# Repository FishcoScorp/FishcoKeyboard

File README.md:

# FishcoKeyboard
My keyboard for the program fallout by hackclub\
\
This keyboard was made with convieniece in mind, with 15 customizable macro keys (4 on left 11 on right) as well as a volume dial and small screen. 

# Table of Contents
Bill of Materials: https://github.com/FishcoScorp/FishcoKeyboard/edit/main/README.md#:~:text=Build_Files-,BOM,-.csv \
Photo Gallery: https://github.com/FishcoScorp/FishcoKeyboard/edit/main/README.md#:~:text=Fallout%20Zine.md-,Photo,-Gallery.md \
Code: https://github.com/FishcoScorp/FishcoKeyboard/edit/main/README.md#:~:text=README.md-,code,-.py \
Zine: https://github.com/FishcoScorp/FishcoKeyboard/edit/main/README.md#:~:text=BOM.csv-,Fallout,-Zine.md \
\
I am also in the process of working on a software that will interface with the keyboard and allow me to easily switch macro keys and the display on the screen, and make it easy to flash new code to the keyboard.\
\

\
How to put it together! \
I used Kicad, and started by making a matrix with all the keys at about where I thought they were on a subsheet. That looks like this (Don't forget to add diodes too!!!) This works by wiring rows and columns which, when shorted by pressing a button, can be identified and pinpointed similar to using x and y on a graph so that it sends the correct input to your device!

\
Then I have the main schematic sheet, where I make all the rest of the connections. Using tags I connect the matrix to the ESP and also the screen and rotary encoder. Notice I connect the grounds of the latter two elements using a GND tag. This is because I am going to use a gnd fill later, which means the board will be coated in a thin layer of copper, removing the need for GND connections as this coating will serve that purpose.

\
Now bring it over to the PCB editor, where you will shape what your keyboard looks like. You can use an app called KB Placer by creating a layout beforehand on the website http://keyboard-layout-editor.com/ and then importing the JSON to KB placer. However, this did not work for me so I had to manually place everything and create the outline of the keyboard myself. I then connected the matrix, rotary encoder, and screen before adding the GND fill (the red in this photo)

\
Then it was time to cad a case. I used Fusion, using the exported .step file model to draw an outline for my case. Then I added some standoffs using the PCB as a reference with the screw holes I had placed earlier, ensuring stabilization but not breaking the PCB. In this case I made so both the bottom and top had walls so that it would look clean and sleek. I also sunk the keys into the keyboard a little so that it would look slim and cool. I also added a window into the ESP cause I think it would look really cool to be abe to see it, a little glimpse into the work/electronics that are required to make this a reality.

\ 
After this I designed my zine and submitted it, and here we are!

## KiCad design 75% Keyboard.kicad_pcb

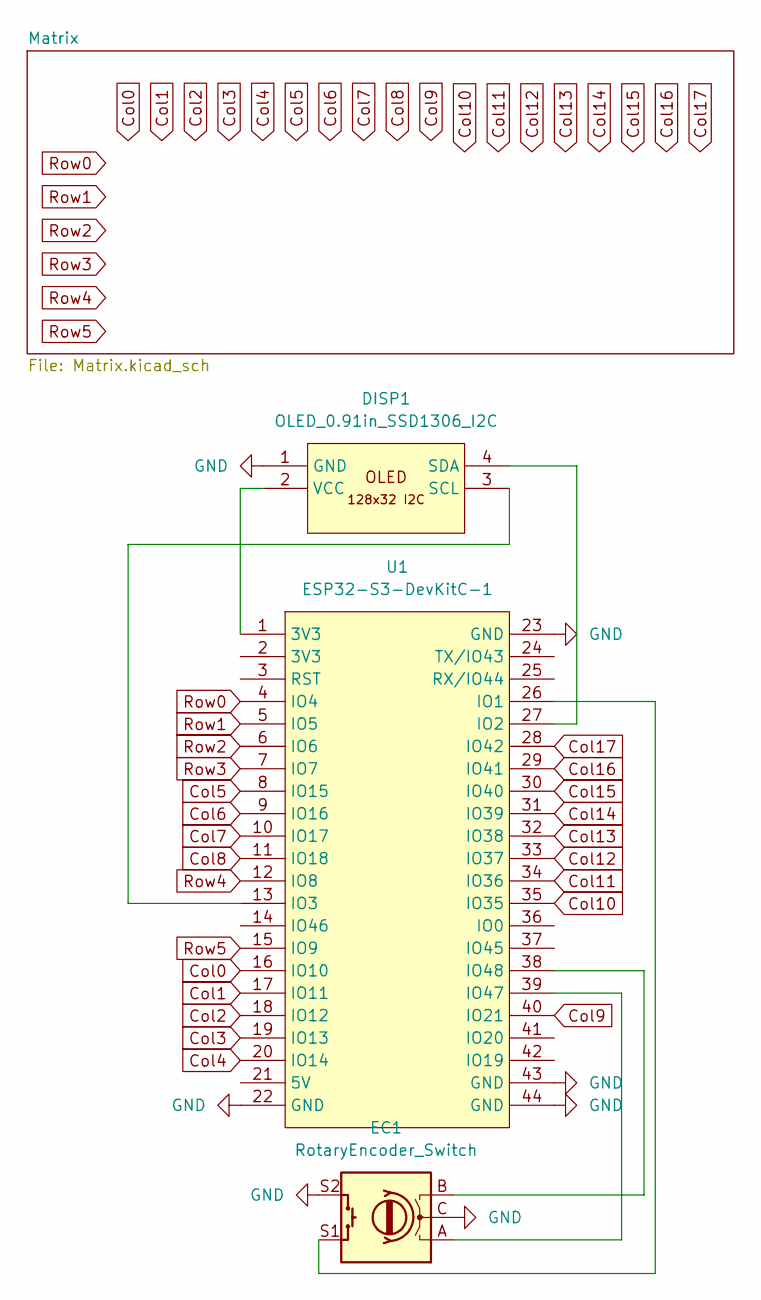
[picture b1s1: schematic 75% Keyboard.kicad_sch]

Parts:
DISP1: OLED_0.91in_SSD1306_I2C; OLED_0.91in_SSD1306_I2C_4Pin_P2.54mm
EC1: RotaryEncoder_Switch; RotaryEncoder_Alps_EC11E-Switch_Vertical_H20mm_MountingHoles
U1: ESP32-S3-DevKitC-1; ESP32-S3-DevKitC-1_2x22_P2.54mm

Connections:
Col0: U1.16 (IO10); also elsewhere on the board
Col1: U1.17 (IO11); also elsewhere on the board
Col2: U1.18 (IO12); also elsewhere on the board
Col3: U1.19 (IO13); also elsewhere on the board
Col4: U1.20 (IO14); also elsewhere on the board
Col5: U1.8 (IO15); also elsewhere on the board
Col6: U1.9 (IO16); also elsewhere on the board
Col7: U1.10 (IO17); also elsewhere on the board
Col8: U1.11 (IO18); also elsewhere on the board
Col9: U1.40 (IO21); also elsewhere on the board
Col10: U1.35 (IO35); also elsewhere on the board
Col11: U1.34 (IO36); also elsewhere on the board
Col12: U1.33 (IO37); also elsewhere on the board
Col13: U1.32 (IO38); also elsewhere on the board
Col14: U1.31 (IO39); also elsewhere on the board
Col15: U1.30 (IO40); also elsewhere on the board
Col16: U1.29 (IO41); also elsewhere on the board
Col17: U1.28 (IO42); also elsewhere on the board
GND: DISP1.1 (GND), EC1.C, EC1.S2, U1.22 (GND), U1.23 (GND), U1.43 (GND), U1.44 (GND)
unnamed: DISP1.3 (SCL), U1.13 (IO3)
unnamed: DISP1.4 (SDA), U1.27 (IO2)
unnamed: DISP1.2 (VCC), U1.1 (3V3)
unnamed: EC1.S1, U1.26 (IO1)
unnamed: EC1.A, U1.39 (IO47)
unnamed: EC1.B, U1.38 (IO48)
Row0: U1.4 (IO4); also elsewhere on the board
Row1: U1.5 (IO5); also elsewhere on the board
Row2: U1.6 (IO6); also elsewhere on the board
Row3: U1.7 (IO7); also elsewhere on the board
Row4: U1.12 (IO8); also elsewhere on the board
Row5: U1.15 (IO9); also elsewhere on the board

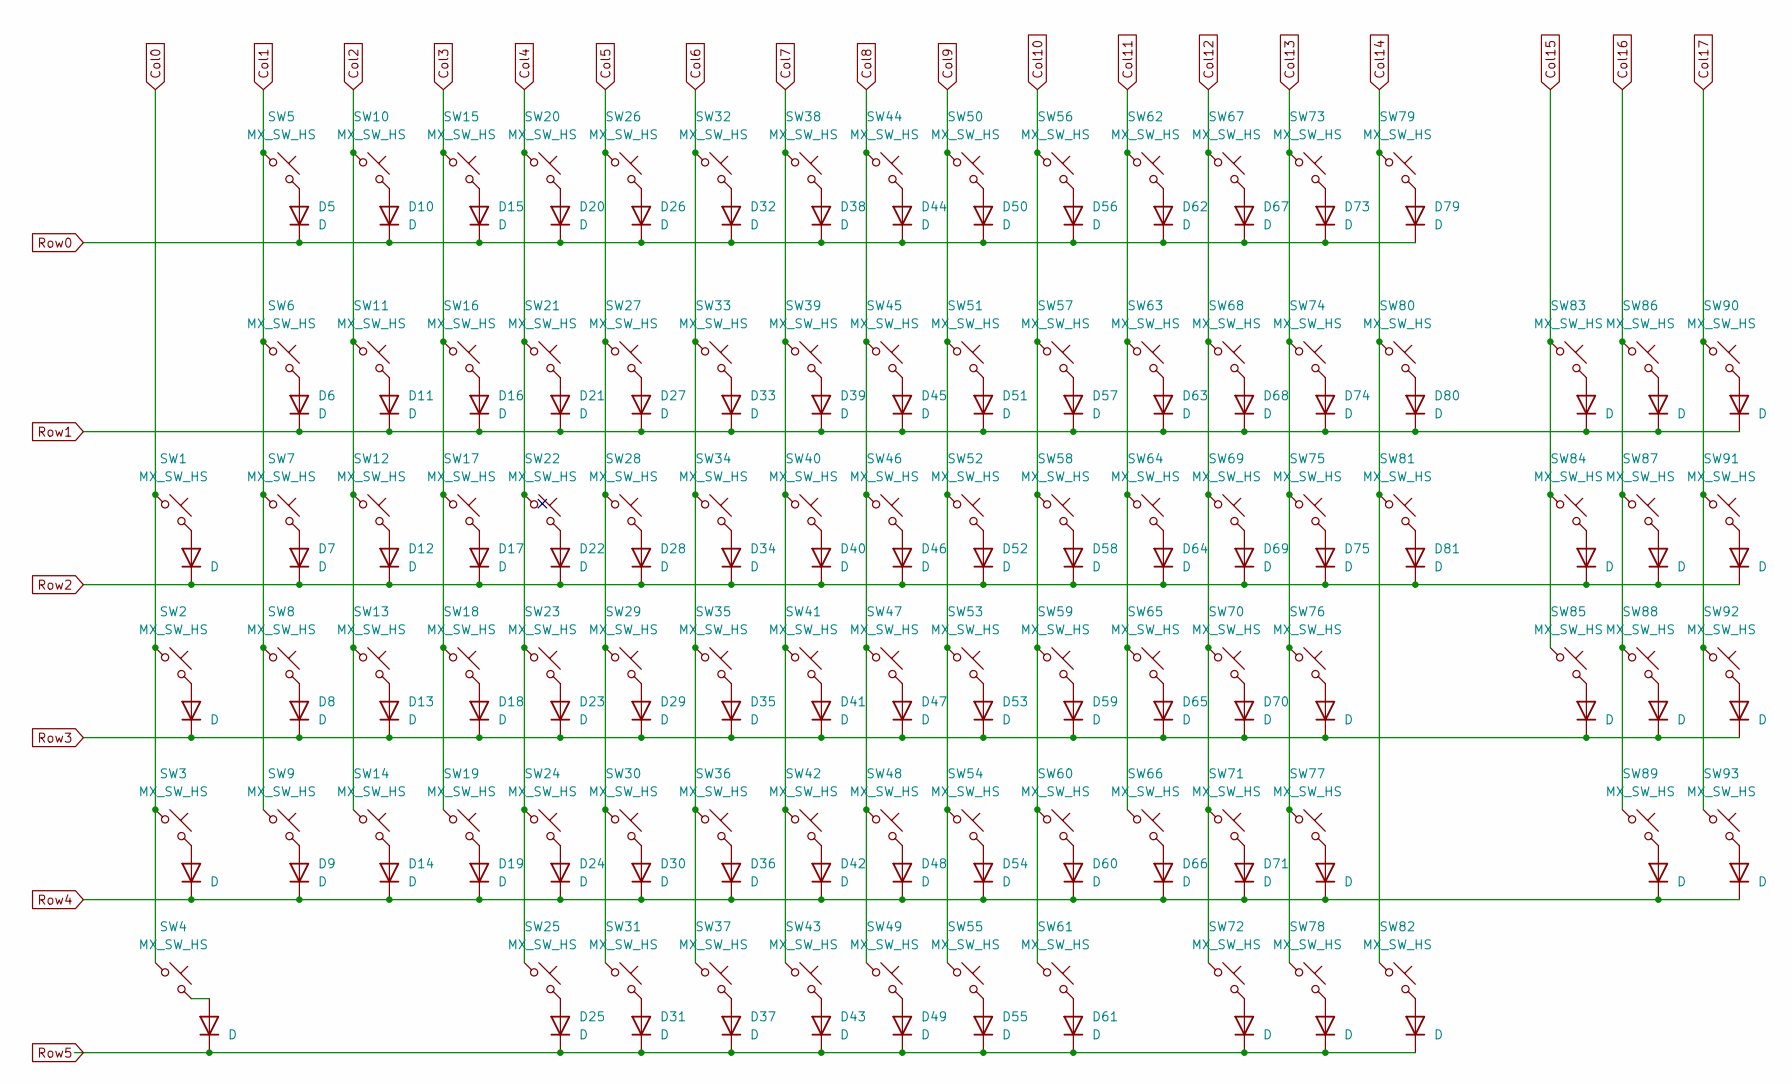
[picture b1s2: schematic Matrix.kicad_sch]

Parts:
D1, D2, D3, D4, D5, D6, D7, D8, D9, D10, D11, D12, D13, D14, D15, D16, D17, D18, D19, D20, D21, D22, D23, D24, D25, D26, D27, D28, D29, D30, D31, D32, D33, D34, D35, D36, D37, D38, D39, D40, D41, D42, D43, D44, D45, D46, D47, D48, D49, D50, D51, D52, D53, D54, D55, D56, D57, D58, D59, D60, D61, D62, D63, D64, D65, D66, D67, D68, D69, D70, D71, D72, D73, D74, D75, D76, D77, D78, D79, D80, D81, D82, D83, D84, D85, D86, D87, D88, D89, D90, D91, D92, D93: D; D_SOD-123
SW1, SW2, SW3, SW4, SW5, SW6, SW10, SW11, SW12, SW13, SW14, SW15, SW16, SW17, SW18, SW19, SW20, SW21, SW22, SW23, SW24, SW26, SW27, SW28, SW29, SW30, SW32, SW33, SW34, SW35, SW36, SW38, SW39, SW40, SW41, SW42, SW44, SW45, SW46, SW47, SW48, SW49, SW50, SW51, SW52, SW53, SW54, SW55, SW56, SW57, SW58, SW59, SW60, SW61, SW62, SW63, SW64, SW65, SW66, SW67, SW68, SW69, SW70, SW72, SW73, SW74, SW75, SW77, SW78, SW79, SW82, SW83, SW84, SW85, SW86, SW87, SW88, SW89, SW90, SW91, SW92, SW93: MX_SW_HS; SW_Cherry_MX_1.00u_PCB
SW7, SW81: MX_SW_HS; SW_Cherry_MX_1.50u_PCB
SW8, SW71: MX_SW_HS; SW_Cherry_MX_1.75u_PCB
SW9, SW76: MX_SW_HS; SW_Cherry_MX_2.25u_PCB
SW25, SW31, SW37: MX_SW_HS; SW_Cherry_MX_1.25u_PCB
SW43: MX_SW_HS; SW_Cherry_MX_6.25u_PCB
SW80: MX_SW_HS; SW_Cherry_MX_2.00u_PCB

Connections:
Col0: SW1.1, SW2.1, SW3.1, SW4.1; also elsewhere on the board
Col1: SW5.1, SW6.1, SW7.1, SW8.1, SW9.1; also elsewhere on the board
Col2: SW10.1, SW11.1, SW12.1, SW13.1, SW14.1; also elsewhere on the board
Col3: SW15.1, SW16.1, SW17.1, SW18.1, SW19.1; also elsewhere on the board
Col4: SW20.1, SW21.1, SW22.1, SW23.1, SW24.1, SW25.1; also elsewhere on the board
Col5: SW26.1, SW27.1, SW28.1, SW29.1, SW30.1, SW31.1; also elsewhere on the board
Col6: SW32.1, SW33.1, SW34.1, SW35.1, SW36.1, SW37.1; also elsewhere on the board
Col7: SW38.1, SW39.1, SW40.1, SW41.1, SW42.1, SW43.1; also elsewhere on the board
Col8: SW44.1, SW45.1, SW46.1, SW47.1, SW48.1, SW49.1; also elsewhere on the board
Col9: SW50.1, SW51.1, SW52.1, SW53.1, SW54.1, SW55.1; also elsewhere on the board
Col10: SW56.1, SW57.1, SW58.1, SW59.1, SW60.1, SW61.1; also elsewhere on the board
Col11: SW62.1, SW63.1, SW64.1, SW65.1, SW66.1; also elsewhere on the board
Col12: SW67.1, SW68.1, SW69.1, SW70.1, SW71.1, SW72.1; also elsewhere on the board
Col13: SW73.1, SW74.1, SW75.1, SW76.1, SW77.1, SW78.1; also elsewhere on the board
Col14: SW79.1, SW80.1, SW81.1, SW82.1; also elsewhere on the board
Col15: SW83.1, SW84.1, SW85.1; also elsewhere on the board
Col16: SW86.1, SW87.1, SW88.1, SW89.1; also elsewhere on the board
Col17: SW90.1, SW91.1, SW92.1, SW93.1; also elsewhere on the board
unnamed: D1.2 (A), SW1.2
unnamed: D2.2 (A), SW2.2
unnamed: D3.2 (A), SW3.2
unnamed: D4.2 (A), SW4.2
unnamed: D5.2 (A), SW5.2
unnamed: D6.2 (A), SW6.2
unnamed: D7.2 (A), SW7.2
unnamed: D8.2 (A), SW8.2
unnamed: D9.2 (A), SW9.2
unnamed: D10.2 (A), SW10.2
unnamed: D11.2 (A), SW11.2
unnamed: D12.2 (A), SW12.2
unnamed: D13.2 (A), SW13.2
unnamed: D14.2 (A), SW14.2
unnamed: D15.2 (A), SW15.2
unnamed: D16.2 (A), SW16.2
unnamed: D17.2 (A), SW17.2
unnamed: D18.2 (A), SW18.2
unnamed: D19.2 (A), SW19.2
unnamed: D20.2 (A), SW20.2
unnamed: D21.2 (A), SW21.2
unnamed: D22.2 (A), SW22.2
unnamed: D23.2 (A), SW23.2
unnamed: D24.2 (A), SW24.2
unnamed: D25.2 (A), SW25.2
unnamed: D26.2 (A), SW26.2
unnamed: D27.2 (A), SW27.2
unnamed: D28.2 (A), SW28.2
unnamed: D29.2 (A), SW29.2
unnamed: D30.2 (A), SW30.2
unnamed: D31.2 (A), SW31.2
unnamed: D32.2 (A), SW32.2
unnamed: D33.2 (A), SW33.2
unnamed: D34.2 (A), SW34.2
unnamed: D35.2 (A), SW35.2
unnamed: D36.2 (A), SW36.2
unnamed: D37.2 (A), SW37.2
unnamed: D38.2 (A), SW38.2
unnamed: D39.2 (A), SW39.2
unnamed: D40.2 (A), SW40.2
unnamed: D41.2 (A), SW41.2
unnamed: D42.2 (A), SW42.2
unnamed: D43.2 (A), SW43.2
unnamed: D44.2 (A), SW44.2
unnamed: D45.2 (A), SW45.2
unnamed: D46.2 (A), SW46.2
unnamed: D47.2 (A), SW47.2
unnamed: D48.2 (A), SW48.2
unnamed: D49.2 (A), SW49.2
unnamed: D50.2 (A), SW50.2
unnamed: D51.2 (A), SW51.2
unnamed: D52.2 (A), SW52.2
unnamed: D53.2 (A), SW53.2
unnamed: D54.2 (A), SW54.2
unnamed: D55.2 (A), SW55.2
unnamed: D56.2 (A), SW56.2
unnamed: D57.2 (A), SW57.2
unnamed: D58.2 (A), SW58.2
unnamed: D59.2 (A), SW59.2
unnamed: D60.2 (A), SW60.2
unnamed: D61.2 (A), SW61.2
unnamed: D62.2 (A), SW62.2
unnamed: D63.2 (A), SW63.2
unnamed: D64.2 (A), SW64.2
unnamed: D65.2 (A), SW65.2
unnamed: D66.2 (A), SW66.2
unnamed: D67.2 (A), SW67.2
unnamed: D68.2 (A), SW68.2
unnamed: D69.2 (A), SW69.2
unnamed: D70.2 (A), SW70.2
unnamed: D71.2 (A), SW71.2
unnamed: D72.2 (A), SW72.2
unnamed: D73.2 (A), SW73.2
unnamed: D74.2 (A), SW74.2
unnamed: D75.2 (A), SW75.2
unnamed: D76.2 (A), SW76.2
unnamed: D77.2 (A), SW77.2
unnamed: D78.2 (A), SW78.2
unnamed: D79.2 (A), SW79.2
unnamed: D80.2 (A), SW80.2
unnamed: D81.2 (A), SW81.2
unnamed: D82.2 (A), SW82.2
unnamed: D83.2 (A), SW83.2
unnamed: D84.2 (A), SW84.2
unnamed: D85.2 (A), SW85.2
unnamed: D86.2 (A), SW86.2
unnamed: D87.2 (A), SW87.2
unnamed: D88.2 (A), SW88.2
unnamed: D89.2 (A), SW89.2
unnamed: D90.2 (A), SW90.2
unnamed: D91.2 (A), SW91.2
unnamed: D92.2 (A), SW92.2
unnamed: D93.2 (A), SW93.2
Row0: D5.1 (K), D10.1 (K), D15.1 (K), D20.1 (K), D26.1 (K), D32.1 (K), D38.1 (K), D44.1 (K), D50.1 (K), D56.1 (K), D62.1 (K), D67.1 (K), D73.1 (K), D79.1 (K); also elsewhere on the board
Row1: D6.1 (K), D11.1 (K), D16.1 (K), D21.1 (K), D27.1 (K), D33.1 (K), D39.1 (K), D45.1 (K), D51.1 (K), D57.1 (K), D63.1 (K), D68.1 (K), D74.1 (K), D80.1 (K), D83.1 (K), D86.1 (K), D90.1 (K); also elsewhere on the board
Row2: D1.1 (K), D7.1 (K), D12.1 (K), D17.1 (K), D22.1 (K), D28.1 (K), D34.1 (K), D40.1 (K), D46.1 (K), D52.1 (K), D58.1 (K), D64.1 (K), D69.1 (K), D75.1 (K), D81.1 (K), D84.1 (K), D87.1 (K), D91.1 (K); also elsewhere on the board
Row3: D2.1 (K), D8.1 (K), D13.1 (K), D18.1 (K), D23.1 (K), D29.1 (K), D35.1 (K), D41.1 (K), D47.1 (K), D53.1 (K), D59.1 (K), D65.1 (K), D70.1 (K), D76.1 (K), D85.1 (K), D88.1 (K), D92.1 (K); also elsewhere on the board
Row4: D3.1 (K), D9.1 (K), D14.1 (K), D19.1 (K), D24.1 (K), D30.1 (K), D36.1 (K), D42.1 (K), D48.1 (K), D54.1 (K), D60.1 (K), D66.1 (K), D71.1 (K), D77.1 (K), D89.1 (K), D93.1 (K); also elsewhere on the board
Row5: D4.1 (K), D25.1 (K), D31.1 (K), D37.1 (K), D43.1 (K), D49.1 (K), D55.1 (K), D61.1 (K), D72.1 (K), D78.1 (K), D82.1 (K); also elsewhere on the board

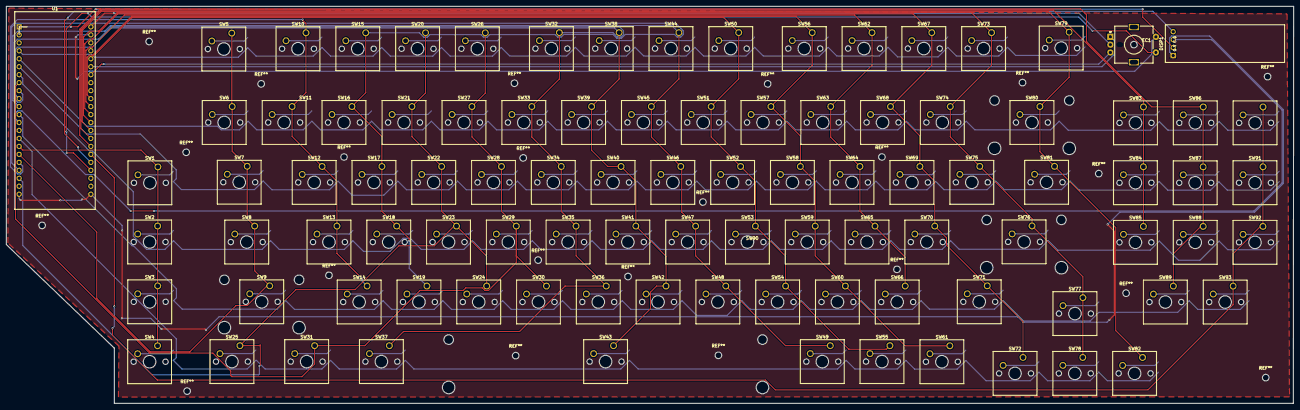
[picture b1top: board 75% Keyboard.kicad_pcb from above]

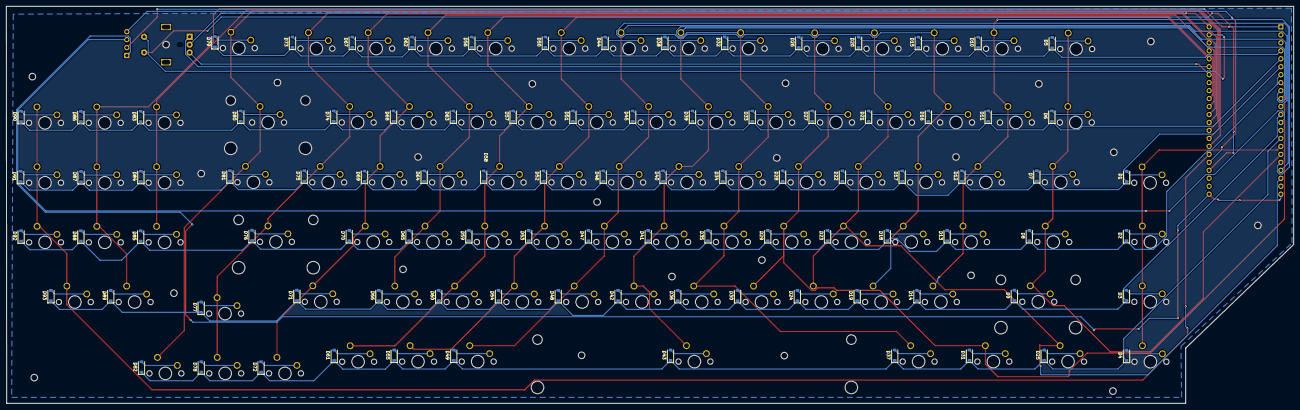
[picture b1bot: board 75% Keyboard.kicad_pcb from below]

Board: 2 copper layers, 410.2 x 126.5 mm, 189 parts (93 on the bottom side), 124 nets.

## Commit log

2026-04-20 Format BOM.md for better readability
2026-04-20 Fix formatting and update purchase links in BOM.md
2026-04-20 Add keyboard matrix and rotary encoder functionality
    Implement a keyboard matrix with rotary encoder support and OLED display.
2026-04-20 Update BOM with new materials and costs
2026-04-20 Add PETG material link to BOM
2026-04-27 Rename 75% Keyboard.kicad_pcb to Build_Files/75% Keyboard.kicad_pcb
2026-04-27 Rename 75% Keyboard.kicad_pcb.zip to Build_Files /75%Keyboard.kicad_pcb.zip
2026-04-27 Rename Fallout Zine (1).png to Fallout Zine.png
2026-04-27 Rename Fallout Zine.png to Fallout Zine.md
2026-04-27 Insert image in Fallout Zine.md
    Add an image to the Fallout Zine document.
2026-04-27 Update README with images and project information
    Added images and updated project details in README.
2026-04-27 Rename BOM.md to BOM.csv
2026-04-27 Add Table of Contents to README
    Added a Table of Contents with links to the Bill of Materials, Photo Gallery, Code, and Zine.
2026-04-27 Fix formatting of links in README.md
2026-04-27 Fix typo in README.md
2026-04-27 Fix spelling and formatting in README.md
    Corrected spelling errors and improved formatting.
2026-04-27 Fix formatting issues in README.md
2026-04-27 Format BOM.csv for better readability
2026-04-27 Add purchase links and update total cost in BOM
    Updated BOM with purchase links for each part and adjusted total cost.
2026-04-27 Update BOM.csv with new part entries
2026-04-27 Rename Fallout Zine.md to FalloutZine.md
2026-04-27 Rename Photo Gallery.md to PhotoGallery.md
2026-05-14 Update PCB manufacturing supplier and total cost
